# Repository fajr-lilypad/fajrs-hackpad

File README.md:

# fajrs-hackpad
This is my hackpad! It is a musicpad, and it had 4 buttons to pause, replay, previous track, and next track, and a rotary encoder to control volume. It also has a OLED screen that will show the track title being played!

I created this macropad so I could easily navigate through a playlist, without having to having to stop what I'm doing to go to spotify in my browser. Though I have experience in CAD, this was my first time using Kicad. Though it took some time and research, I was able to get my pcb done!

BOM:
- 4x Cherry MX Switches
- 1x Seeed XIAO RP2040
- 4x Blank DSA Keycaps
- 1x EC11 Rotary Encoder
- 4x Through-hole 1N4148 Diodes
- 1x 0.91 inch OLED display
- 4x SK6812 MINI-E RGB LEDs
- 4x M3×16mm screws
- 4x M3 heatset inserts (5mm × 4mm)

Schematic            |  PCB         |   Case
:-------------------------:|:-------------------------:|:-------------------------:|
  |   |

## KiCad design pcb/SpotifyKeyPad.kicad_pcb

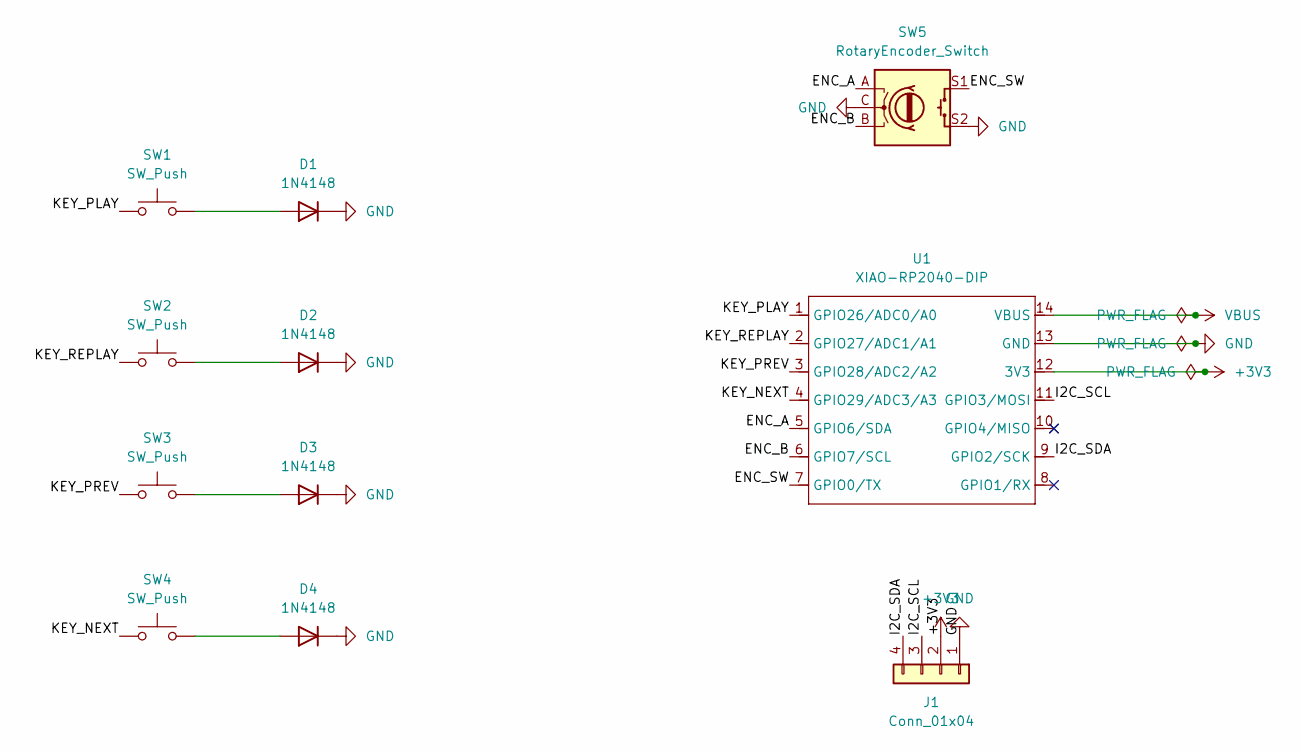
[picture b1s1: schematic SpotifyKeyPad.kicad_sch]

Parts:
D1, D2, D3, D4: 1N4148; D_DO-35_SOD27_P7.62mm_Horizontal
J1: Conn_01x04; PinHeader_1x04_P2.54mm_Vertical
SW1, SW2, SW3, SW4: SW_Push; SW_Cherry_MX_1.00u_PCB
SW5: RotaryEncoder_Switch; RotaryEncoder_Alps_EC11E-Switch_Vertical_H20mm
U1: XIAO-RP2040-DIP

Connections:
+3V3: J1.2, U1.12 (3V3)
/ENC_A: SW5.A, U1.5 (GPIO6/SDA)
/ENC_B: SW5.B, U1.6 (GPIO7/SCL)
/ENC_SW: SW5.S1, U1.7 (GPIO0/TX)
/I2C_SCL: J1.3, U1.11 (GPIO3/MOSI)
/I2C_SDA: J1.4, U1.9 (GPIO2/SCK)
/KEY_NEXT: SW4.1, U1.4 (GPIO29/ADC3/A3)
/KEY_PLAY: SW1.1, U1.1 (GPIO26/ADC0/A0)
/KEY_PREV: SW3.1, U1.3 (GPIO28/ADC2/A2)
/KEY_REPLAY: SW2.1, U1.2 (GPIO27/ADC1/A1)
GND: D1.1 (K), D2.1 (K), D3.1 (K), D4.1 (K), J1.1, SW5.C, SW5.S2, U1.13 (GND)
unnamed: D1.2 (A), SW1.2
unnamed: D2.2 (A), SW2.2
unnamed: D3.2 (A), SW3.2
unnamed: D4.2 (A), SW4.2
VBUS: U1.14 (VBUS)

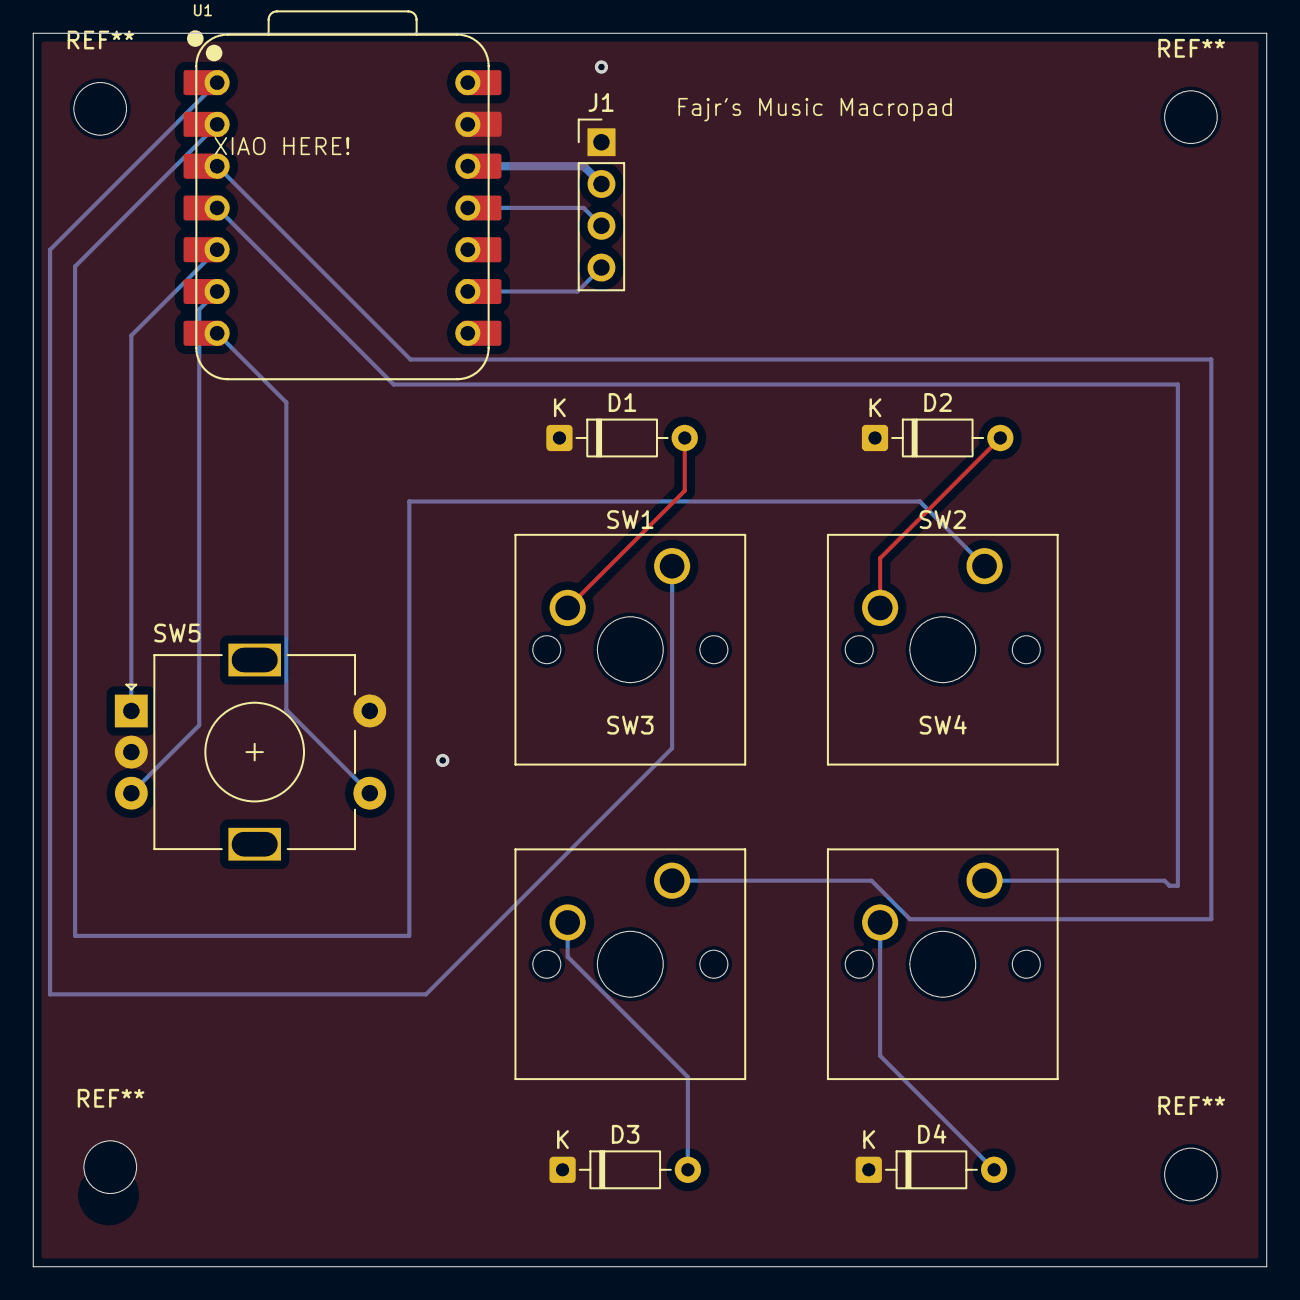
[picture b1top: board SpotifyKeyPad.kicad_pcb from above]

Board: 2 copper layers, 75.0 x 75.0 mm, 11 parts (0 on the bottom side), 15 nets.

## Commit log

2025-12-26 README.md
2025-12-26 Rename Screenshot 2025-12-25 202812.png to images/Screenshot 2025-12-25 202812.png
2025-12-26 Rename Screenshot 2025-12-25 202812.png to Schematic Screenshot
2025-12-26 Rename Schematic Screenshot to Schematic-Screenshot
2025-12-26 Rename Schematic-Screenshot to schematic screenshot
2025-12-26 Create read
